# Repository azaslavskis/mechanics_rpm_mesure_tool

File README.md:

# Mechanics RPM Measurement Tool

This simple device, built using an Arduino Nano and an A3144 Hall sensor, allows you to measure the RPM (Revolutions Per Minute) of a gear. The device is straightforward to construct and program, making it an excellent project for hobbyists and engineers alike.

---

## Schematic

The circuit is simple and consists of just two resistors, an A3144 Hall sensor, and an LED. Below is the basic schematic:

---

## Bill of Materials (BOM)

Here’s what you’ll need to build the device:

1. **1x Arduino Nano** – The microcontroller that processes the sensor readings.
2. **2x 1 kΩ Resistors** – For pull-up configuration and current limiting.
3. **1x A3144 Hall Sensor** – To detect magnetic pulses from the rotating gear.
4. **1x Breadboard** – For quick prototyping.
5. **Wires and Glue** – To secure connections during experiments.

---

## Software

The project consists of two main software components:

1. **Arduino Firmware**:
   - This code is uploaded to the Arduino Nano using the Arduino IDE.
   - It reads data from the Hall sensor and calculates the RPM or time between pulses.
   - Configuration options are available via `#define` directives in the firmware for customization.

2. **CLI Data Plotting Tool** (written in Rust):
   - This command-line tool plots the RPM data as a graph.
   - It also saves the data to a `data.txt` file for further analysis or post-processing.

---

## Demo

Here’s a demonstration of the device in action:

### Graph Plot
The CLI tool generates a live graph showing the RPM data in real time.

### Device Appearance
The device assembly is minimal and effective. To ensure stable connections during experiments, glue was used to secure the wires.

### Video Demonstration
Watch the device in action:

---

This project is a cost-effective and straightforward way to measure RPM, making it a practical solution for various mechanical experiments and applications. With easy-to-follow schematics, a minimal BOM, and robust software support, it’s perfect for anyone looking to explore or enhance their understanding of rotational speed measurement.

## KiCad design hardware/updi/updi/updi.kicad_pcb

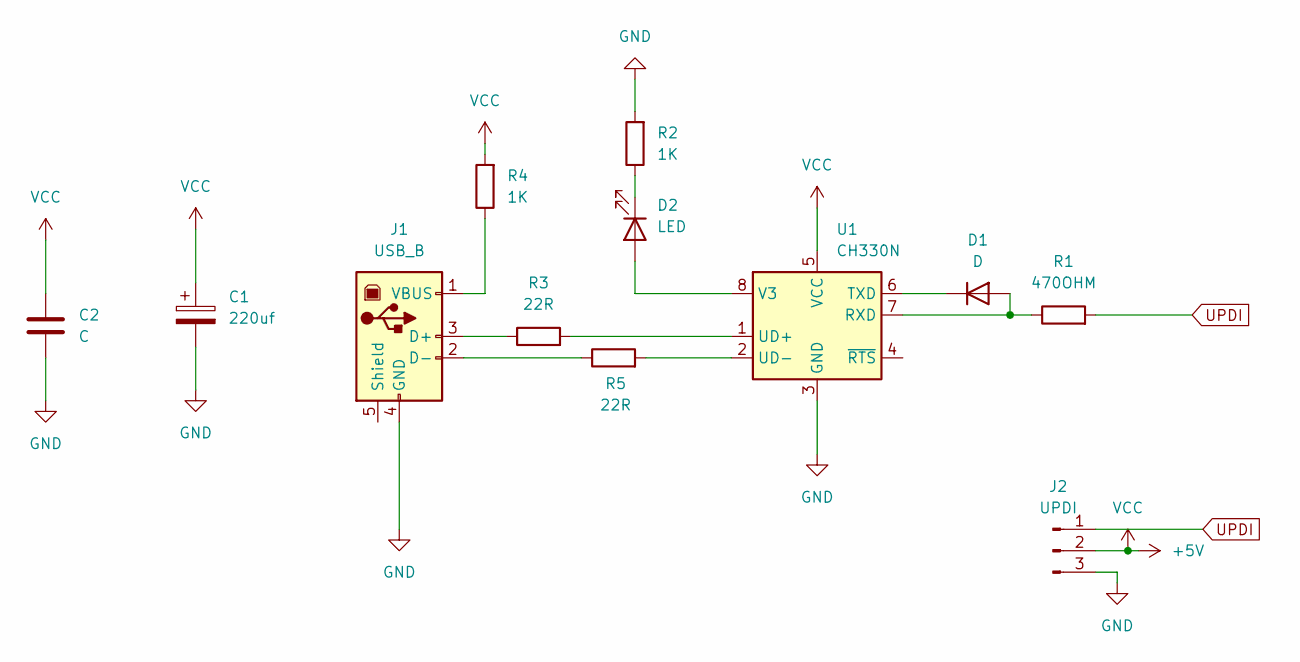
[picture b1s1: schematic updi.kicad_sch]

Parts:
C1: 220uf; CP_Radial_D5.0mm_P2.50mm
C2: C; C_Rect_L4.6mm_W2.0mm_P2.50mm_MKS02_FKP02
D1: D; D_5W_P12.70mm_Horizontal
D2: LED; LED_D3.0mm
J1: USB_B; USB_B_Lumberg_2411_02_Horizontal
J2: UPDI; JST_XH_B3B-XH-AM_1x03_P2.50mm_Vertical
R1: 470OHM; R_Axial_DIN0204_L3.6mm_D1.6mm_P7.62mm_Horizontal
R2, R4: 1K; R_Axial_DIN0204_L3.6mm_D1.6mm_P7.62mm_Horizontal
R3, R5: 22R; R_Axial_DIN0204_L3.6mm_D1.6mm_P7.62mm_Horizontal
U1: CH330N; SOIC-8_3.9x4.9mm_P1.27mm

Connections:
+5V: C1.1, C2.1, J2.2, R4.2, U1.5 (VCC)
GND: C1.2, C2.2, J1.4 (GND), J2.3, R2.2, U1.3 (GND)
unnamed: D1.2 (A), R1.1, U1.7 (RXD)
unnamed: D1.1 (K), U1.6 (TXD)
unnamed: D2.2 (A), U1.8 (V3)
unnamed: D2.1 (K), R2.1
unnamed: J1.3 (D+), R3.1
unnamed: J1.2 (D-), R5.1
unnamed: J1.1 (VBUS), R4.1
unnamed: R3.2, U1.1 (UD+)
unnamed: R5.2, U1.2 (UD-)
UPDI: J2.1, R1.2

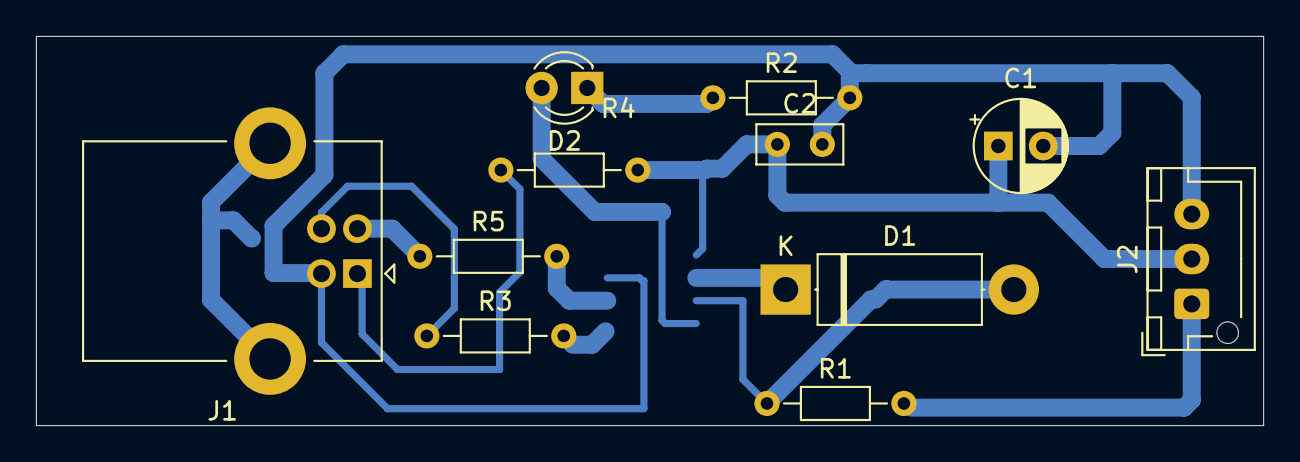
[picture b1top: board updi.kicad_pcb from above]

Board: 2 copper layers, 68.3 x 21.7 mm, 12 parts (1 on the bottom side), 12 nets.

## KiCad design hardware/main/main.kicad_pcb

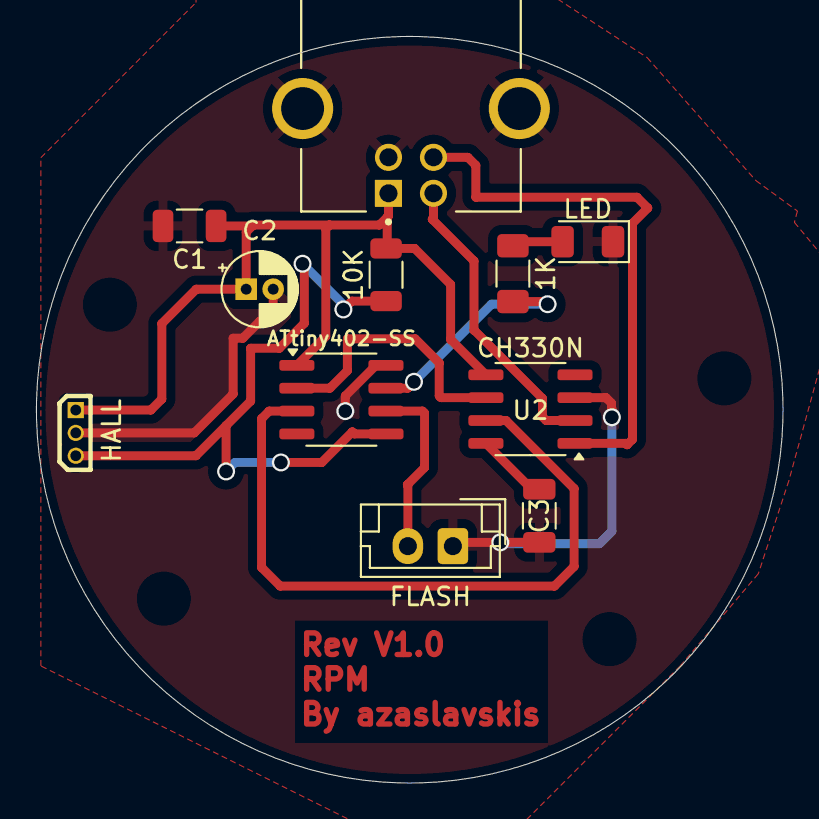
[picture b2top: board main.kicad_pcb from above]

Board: 2 copper layers, 41.5 x 41.5 mm, 11 parts (0 on the bottom side), 11 nets.

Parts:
ATtiny402-SS: ATtiny402-SS; SOIC-8_3.9x4.9mm_P1.27mm
C1, C3: C; C_1206_3216Metric
C2: C_Polarized; CP_Radial_D4.0mm_P1.50mm
D1: LED; LED_1206_3216Metric
FLASH: FLASH; JST_EH_B2B-EH-A_1x02_P2.50mm_Vertical
HALL: A3144EUA-T-JSM; TO-92S-3_L4.1-W1.7-P1.27-L
J1: 61729-1010BLF; AMPHENOL_61729-1010BLF
R1: 1K; R_1206_3216Metric_Pad1.30x1.75mm_HandSolder
R2: 10K; R_1206_3216Metric
U2: CH330N; SOIC-8_3.9x4.9mm_P1.27mm

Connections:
D+: J1.3 (D+), U2.1 (UD+)
D-: J1.2 (D-), U2.2 (UD-)
GND: ATtiny402-SS.8 (GND), C1.2, C2.2, C3.1, D1.1 (K), FLASH.1, HALL.2 (GND), J1.4 (GND), J1.SH1 (SHIELD), J1.SH2 (SHIELD__1), U2.3 (GND)
unnamed: D1.2 (A), R1.2
unnamed: ATtiny402-SS.7 (PA3), R1.1
unnamed: C3.2, U2.8 (V3)
OUT: ATtiny402-SS.5 (PA2), HALL.3 (VOUT), R2.2
RESET: ATtiny402-SS.6 (~RESET/PA0), FLASH.2
RX: ATtiny402-SS.2 (PA6), U2.6 (TXD)
TX: ATtiny402-SS.3 (PA7), U2.7 (RXD)
VCC: ATtiny402-SS.1 (VCC), C1.1, C2.1, HALL.1 (VSUP), J1.1 (VCC), R2.1, U2.5 (VCC)

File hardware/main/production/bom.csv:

Designator,Footprint,Quantity,Value,LCSC Part #
ATtiny402-SS,SOIC-8_3.9x4.9mm_P1.27mm,1,ATtiny402-SS,
"C1, C3",1206,2,C,
C2,CP_Radial_D4.0mm_P1.50mm,1,C_Polarized,
D1,1206,1,LED,
FLASH,JST_EH_B2B-EH-A_1x02_P2.50mm_Vertical,1,FLASH,
HALL,TO-92S-3_L4.1-W1.7-P1.27-L,1,A3144EUA-T-JSM,C18188954
J1,AMPHENOL_61729-1010BLF,1,61729-1010BLF,
R1,1206,1,1K,
R2,1206,1,10K,
U2,SOIC-8_3.9x4.9mm_P1.27mm,1,CH330N,

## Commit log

2022-12-06 added firmware
2022-12-06 added cli software & build script
2024-11-16 draweed simple pcb for it
2024-11-16 final pcb version
2024-11-16 added holdes
2024-11-16 final version
2024-11-18 UPDI
2024-11-20 Fixed README.md
